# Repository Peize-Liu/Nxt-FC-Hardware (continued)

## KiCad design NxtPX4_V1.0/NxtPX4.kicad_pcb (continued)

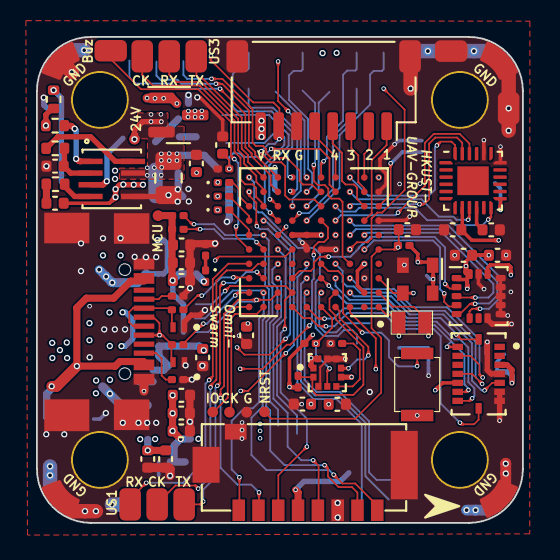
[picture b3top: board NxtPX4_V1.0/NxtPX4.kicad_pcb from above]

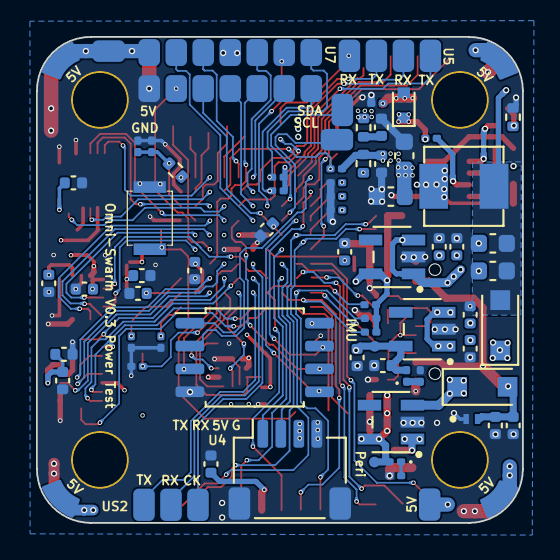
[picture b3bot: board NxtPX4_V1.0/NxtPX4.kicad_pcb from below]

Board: 4 copper layers, 27.0 x 27.0 mm, 150 parts (73 on the bottom side), 115 nets.

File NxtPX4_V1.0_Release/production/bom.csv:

Designator,Footprint,Quantity,Value,LCSC Part #
"BOOT1, RST1",3x2.5PushButton,2,TD-1183SN-1.5H(3x2.5),
C1,C_0805_2012Metric,1,22uF(0805 35V),
"C10, C16, C17, C19",C_0402_1005Metric,4,1uF(0402),
"C11, C12, C13, C14, C18, C20, C21, C22, C23, C24, C25, C28, C36, C39, C40, C42, C44, C46, C48, C49, C51, C6, C7, C8, C9",C_0402_1005Metric,25,100nF(0402),
"C15, C3, C41, C45",C_0402_1005Metric,4,10nF(0402),
"C2, C4",C_0603_1608Metric,2,10uF(0603 35V),
"C26, C27",C_0603_1608Metric,2,22uF(0603),
"C29, C30, C43",C_0402_1005Metric,3,2.2uF(0402),
C31,C_0402_1005Metric,1,4.7uF(0402),
C32,C_0402_1005Metric,1,15pF(0402),
C33,C_0402_1005Metric,1,1.0uF(0402),
C34,C_0201_0603Metric,1,100nF(0201),
C35,C_0201_0603Metric,1,1uF(0201),
"C37, C38",C_0201_0603Metric,2,12.0pF(0201),
"C47, C50",C_0402_1005Metric,2,100.0nF(0402),
C5,C_0402_1005Metric,1,1uF(0402 35V),
D1,PESD12VV1BL_315,1,PESD12VV1BL,
D10,LED_0201_0603Metric,1,LED_RED(0201),
D11,LED_0201_0603Metric,1,LED_BLUE(0201),
D12,LED_0201_0603Metric,1,LED_GREEN(0201),
"D2, D3",PESD5V0F1BL,2,PESD5V0F1BL,
D4,D_SOD-523,1,BZX584C9V1,
"D5, D6",D_SOD-123F,2,DSS34,
"D7, D8, D9",LED_0201_0603Metric,3,LED_G(0201),
J1,USB-C-16p,1,USB_C_Receptacle_USB2.0,
J10,JST_SH_SM08B-SRSS-TB_1x08-1MP_P1.00mm_Horizontal,1,ESC sh1.0 8pin,
J11,TF-SMD_TF-021B-H265,1,Micro_SD_Card,
J2,Conn_4Pin,1,Conn_01x04,
"J4, J5, J6",Conn_3pin,3,Conn_01x03,
J8,Conn_14pin,1,Conn_01x14,
J9,JST_SH_SM04B-SRSS-TB_1x04-1MP_P1.00mm_Horizontal,1,UART4(sh1.0 4pin),
L1,Inductor_0420,1,10uH(0420),
Q1,SOT-23,1,AP40P05,
"R1, R9",R_0402_1005Metric,2,33R(0402),
R10,R_0402_1005Metric,1,20R(0402),
R11,R_0402_1005Metric,1,51kR(0402),
R12,R_0402_1005Metric,1,7.68kR(0402),
R13,R_0402_1005Metric,1,41.2kR(0402),
R14,R_0201_0603Metric,1,200.0kR(0201),
R15,R_0201_0603Metric,1,22.0kR(0201),
"R16, R17, R18, R24, R26, R30, R31, R32, R33, R34",R_0201_0603Metric,10,10kR(0201),
"R19, R20, R27, R28",R_0201_0603Metric,4,4.7kR(0201),
"R2, R3",R_0201_0603Metric,2,5.1kR(0201),
"R21, R22, R23",R_0201_0603Metric,3,10.0kR(0201),
R25,R_0402_1005Metric,1,0.0R(0402),
"R29, R5, R6",R_0201_0603Metric,3,0R(0201),
R4,R_0201_0603Metric,1,100kR(0201),
R7,R_0201_0603Metric,1,1mR(0201),
R8,R_0402_1005Metric,1,100kR(0402),
"TP10, TP11, TP12, TP13, TP6, TP7, TP8, TP9",PWR_Circle,8,TestPoint,
"TP24, TP26, TP28",Conn_1pin,3,TestPoint,
TP25,Conn_1pin,1,5V_TP,
TP27,Conn_1pin,1,GND_TP,
"TP29, TP30, TP31, TP32",MiniTP,4,TestPoint,
TP5,MiniTP,1,24V_TP,
"U1, U2, U3",RT9013-33GB,3,RT9013-33GB,
U10,BMI088,1,BMI088,
U11,SOIC-8_5.23x5.23mm_P1.27mm,1,W25Q128JVS,
U4,MP9943GQ-Z,1,MP9943GQ-Z,
U6,STM32H743VIHBGA100C80P10X10_800X800X110N,1,STM32H743VIH6,
U7,QFN-24-1EP_3x3mm_P0.4mm_EP1.75x1.6mm,1,MPU6500,
U8,LGA-16_3x3mm_P0.5mm_LayoutBorder3x5y,1,ICM-20602,
U9,PQFN50P200X200X80-10N,1,BMP388,
Y1,Oscillator_SMD_Abracon_ASDMB-4Pin_2.5x2.0mm,1,SG-210STF,
Y2,LSE(2012),1,ABS07 (32.768kHZ),

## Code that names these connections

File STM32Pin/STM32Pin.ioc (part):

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Mcu.Name=STM32H743VITx
Mcu.Package=LQFP100
Mcu.UserName=STM32H743VITx
PA0.GPIOParameters=GPIO_Label,PinAttribute
PA0.GPIO_Label=PWM/DSHOT CH1
PA0.PinAttribute=Free
PA0.Signal=S_TIM5_CH1
PA1.GPIOParameters=GPIO_Label,PinAttribute
PA1.GPIO_Label=PWM/DSHOT CH2
PA1.PinAttribute=Free
PA1.Signal=S_TIM5_CH2
PA11.Mode=Device_Only
PA11.Signal=USB_OTG_FS_DM
PA12.Mode=Device_Only
PA12.Signal=USB_OTG_FS_DP
PA13\ (JTMS/SWDIO).Mode=Serial_Wire
PA13\ (JTMS/SWDIO).Signal=DEBUG_JTMS-SWDIO
PA14\ (JTCK/SWCLK).Mode=Serial_Wire
PA14\ (JTCK/SWCLK).Signal=DEBUG_JTCK-SWCLK
PA2.GPIOParameters=GPIO_Label,PinAttribute
PA2.GPIO_Label=PWM/DSHOT CH3
PA2.PinAttribute=Free
PA2.Signal=S_TIM5_CH3
PA3.GPIOParameters=GPIO_Label,PinAttribute
PA3.GPIO_Label=PWM/DSHOT CH4
PA3.PinAttribute=Free
PA3.Signal=S_TIM5_CH4
PA4.GPIOParameters=PinAttribute
PA4.Mode=Synchronous
PA4.PinAttribute=Free
PA4.Signal=USART2_CK
PA5.GPIOParameters=PinAttribute
PA5.Mode=Full_Duplex_Master
PA5.PinAttribute=Free
PA5.Signal=SPI1_SCK
PA6.GPIOParameters=PinAttribute
PA6.Mode=Full_Duplex_Master
PA6.PinAttribute=Free
PA6.Signal=SPI1_MISO
PA7.GPIOParameters=GPIO_Label,PinAttribute
PA7.GPIO_Label=MPU_Data_RDY
PA7.PinAttribute=Free
PA7.Signal=GPXTI7
PA8.Mode=Synchronous
PA8.Signal=USART1_CK
PA9.Mode=Full_Duplex_Master
PA9.Signal=SPI2_SCK
PB0.GPIOParameters=GPIO_Label,PinAttribute
PB0.GPIO_Label=BAT_V
PB0.PinAttribute=Free
PB0.Signal=ADCx_INP9
PB1.GPIOParameters=GPIO_Label,PinAttribute
PB1.GPIO_Label=BAT_I
PB1.PinAttribute=Free
PB1.Signal=ADCx_INP5
PB10.GPIOParameters=PinAttribute
PB10.Mode=I2C
PB10.PinAttribute=Free
PB10.Signal=I2C2_SCL
PB11.Mode=I2C
PB11.Signal=I2C2_SDA
PB12.GPIOParameters=PinAttribute
PB12.Mode=Asynchronous
PB12.PinAttribute=Free
PB12.Signal=UART5_RX
PB13.Mode=Asynchronous
PB13.Signal=UART5_TX
PB14.Mode=Synchronous
PB14.Signal=USART1_TX
PB15.Mode=Synchronous
PB15.Signal=USART1_RX
PB2.GPIOParameters=PinAttribute
PB2.Mode=Single Bank 1
PB2.PinAttribute=Free
PB2.Signal=QUADSPI_CLK
PB3\ (JTDO/TRACESWO).Mode=Full_Duplex_Master
PB3\ (JTDO/TRACESWO).Signal=SPI3_SCK
PB4\ (NJTRST).Mode=Full_Duplex_Master
PB4\ (NJTRST).Signal=SPI3_MISO
PB5.Mode=Full_Duplex_Master
PB5.Signal=SPI3_MOSI
PB6.Mode=Single Bank 1
PB6.Signal=QUADSPI_BK1_NCS
PB7.Mode=I2C
PB7.Signal=I2C1_SDA
PB8.Mode=I2C
PB8.Signal=I2C1_SCL
PB9.GPIOParameters=GPIO_Label
PB9.GPIO_Label=BMP_Data_RDY
PB9.Signal=GPXTI9
PC0.GPIOParameters=GPIO_Label
PC0.GPIO_Label=ICM_Data_RDY
PC0.Signal=GPXTI0
PC1.Mode=Full_Duplex_Master
PC1.Signal=SPI2_MOSI
PC10.Mode=SD_4_bits_Wide_bus
PC10.Signal=SDMMC1_D2
PC11.Mode=SD_4_bits_Wide_bus
PC11.Signal=SDMMC1_D3
PC12.Mode=SD_4_bits_Wide_bus
PC12.Signal=SDMMC1_CK
PC13.GPIOParameters=GPIO_Label
PC13.GPIO_Label=Extern_SPI_INT_2
PC13.Signal=GPIO_Input
PC14-OSC32_IN\ (OSC32_IN).Mode=LSE-External-Oscillator
PC14-OSC32_IN\ (OSC32_IN).Signal=RCC_OSC32_IN
PC15-OSC32_OUT\ (OSC32_OUT).Mode=LSE-External-Oscillator
PC15-OSC32_OUT\ (OSC32_OUT).Signal=RCC_OSC32_OUT
PC2_C.Mode=Full_Duplex_Master
PC2_C.Signal=SPI2_MISO
PC3_C.GPIOParameters=GPIO_Label,PinAttribute
PC3_C.GPIO_Label=ICM_NCS
PC3_C.PinAttribute=Free
PC3_C.Signal=GPIO_Output
PC4.GPIOParameters=GPIO_Label,PinAttribute
PC4.GPIO_Label=MPU_NCS
PC4.PinAttribute=Free
PC4.Signal=GPIO_Output
PC7.GPIOParameters=GPIO_Label
PC7.GPIO_Label=Buzzer
PC7.Signal=S_TIM3_CH2
PC8.Mode=SD_4_bits_Wide_bus
PC8.Signal=SDMMC1_D0
PC9.Mode=SD_4_bits_Wide_bus
PC9.Signal=SDMMC1_D1
PD0.Mode=Asynchronous
PD0.Signal=UART4_RX
PD1.Mode=Asynchronous
PD1.Signal=UART4_TX
PD10.Mode=Synchronous
PD10.Signal=USART3_CK
PD11.Mode=Single Bank 1
PD11.Signal=QUADSPI_BK1_IO0
PD12.Mode=Single Bank 1
PD12.Signal=QUADSPI_BK1_IO1
PD13.Mode=Single Bank 1
PD13.Signal=QUADSPI_BK1_IO3
PD14.GPIOParameters=GPIO_Label
PD14.GPIO_Label=PWM/DSHOT CH5
PD14.Signal=S_TIM4_CH3
PD15.GPIOParameters=GPIO_Label
PD15.GPIO_Label=PWM/DSHOT CH6 
PD15.Signal=S_TIM4_CH4
PD2.Mode=SD_4_bits_Wide_bus
PD2.Signal=SDMMC1_CMD
PD3.GPIOParameters=GPIO_Label
PD3.GPIO_Label=BMI_Accel_CS
PD3.Signal=GPIO_Output
PD4.GPIOParameters=GPIO_Label
PD4.GPIO_Label=BMI_Gyro_CS
PD4.Signal=GPIO_Output
PD5.Mode=Synchronous
PD5.Signal=USART2_TX
PD6.Mode=Synchronous
PD6.Signal=USART2_RX
PD7.Mode=Full_Duplex_Master
PD7.Signal=SPI1_MOSI
PD8.Mode=Synchronous
PD8.Signal=USART3_TX
PD9.Mode=Synchronous
PD9.Signal=USART3_RX
PE0.GPIOParameters=GPIO_Label
PE0.GPIO_Label=BMI_Accel_Data_RDY
PE0.Signal=GPIO_Output
PE1.GPIOParameters=GPIO_Label
PE1.GPIO_Label=BMI_Gyro_Data_RDY
PE1.Signal=GPIO_Output
PE11.GPIOParameters=GPIO_Label,PinAttribute
PE11.GPIO_Label=Extern_I2C_INT
PE11.PinAttribute=Free
PE11.Signal=GPXTI11
PE12.GPIOParameters=PinAttribute
PE12.Mode=Full_Duplex_Master
PE12.PinAttribute=Free
PE12.Signal=SPI4_SCK
PE13.GPIOParameters=GPIO_Label,PinAttribute
PE13.GPIO_Label=Status_LED_RED
PE13.PinAttribute=Free
PE13.Signal=GPIO_Output
PE14.GPIOParameters=GPIO_Label,PinAttribute
PE14.GPIO_Label=Status_LED_BLUE
PE14.PinAttribute=Free
PE14.Signal=GPIO_Analog
PE15.GPIOParameters=GPIO_Label,PinAttribute
PE15.GPIO_Label=Status_LED_GREEN
PE15.PinAttribute=Free
PE15.Signal=GPIO_Output
PE2.Mode=Single Bank 1
PE2.Signal=QUADSPI_BK1_IO2
PE3.GPIOParameters=GPIO_Label
PE3.GPIO_Label=Extern_SPI_INT_1
PE3.Signal=GPXTI3
PE4.GPIOParameters=GPIO_Label
PE4.GPIO_Label=Extern_SPI_CS_2
PE4.Signal=GPIO_Output
PE5.Mode=Full_Duplex_Master
PE5.Signal=SPI4_MISO
PE6.Mode=Full_Duplex_Master
PE6.Signal=SPI4_MOSI
PE7.GPIOParameters=PinAttribute
PE7.Mode=Asynchronous
PE7.PinAttribute=Free
PE7.Signal=UART7_RX
PE8.GPIOParameters=PinAttribute
PE8.Mode=Asynchronous
PE8.PinAttribute=Free
PE8.Signal=UART7_TX
PE9.GPIOParameters=GPIO_Label,PinAttribute
PE9.GPIO_Label=Extern_IMU_Heater
PE9.PinAttribute=Free
PE9.Signal=S_TIM1_CH1
PH0-OSC_IN\ (PH0).Mode=HSE-External-Clock-Source
PH0-OSC_IN\ (PH0).Signal=RCC_OSC_IN
PH1-OSC_OUT\ (PH1).GPIOParameters=GPIO_Label
PH1-OSC_OUT\ (PH1).GPIO_Label=Extern_SPI_CS_1
PH1-OSC_OUT\ (PH1).Signal=GPIO_Output
RCC.HSE_VALUE=16000000
RCC.SYSCLKFreq_VALUE=480000000
RCC.SYSCLKSource=RCC_SYSCLKSOURCE_PLLCLK
board=custom

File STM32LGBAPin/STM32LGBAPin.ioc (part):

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Mcu.Name=STM32H743V(G-I)Hx
Mcu.Package=TFBGA100
Mcu.UserName=STM32H743VIHx
PA0.Signal=S_TIM5_CH1
PA1.Signal=S_TIM5_CH2
PA10.Mode=Synchronous
PA10.Signal=USART1_RX
PA11.Mode=Device_Only
PA11.Signal=USB_OTG_FS_DM
PA12.Mode=Device_Only
PA12.Signal=USB_OTG_FS_DP
PA13\ (JTMS/SWDIO).Mode=Serial_Wire
PA13\ (JTMS/SWDIO).Signal=DEBUG_JTMS-SWDIO
PA14\ (JTCK/SWCLK).Mode=Serial_Wire
PA14\ (JTCK/SWCLK).Signal=DEBUG_JTCK-SWCLK
PA2.Signal=S_TIM5_CH3
PA3.Signal=S_TIM5_CH4
PA4.GPIOParameters=GPIO_Label
PA4.GPIO_Label=SPI2_Data_RDY
PA4.Signal=GPXTI4
PA5.Mode=Full_Duplex_Master
PA5.Signal=SPI1_SCK
PA6.Mode=Full_Duplex_Master
PA6.Signal=SPI1_MISO
PA7.Mode=Full_Duplex_Master
PA7.Signal=SPI1_MOSI
PA8.Mode=Synchronous
PA8.Signal=USART1_CK
PA9.Mode=Synchronous
PA9.Signal=USART1_TX
PB0.GPIOParameters=GPIO_Label
PB0.GPIO_Label=BAT_V
PB0.Signal=ADCx_INP9
PB1.GPIOParameters=GPIO_Label
PB1.GPIO_Label=BAT_I
PB1.Signal=ADCx_INP5
PB10.Mode=I2C
PB10.Signal=I2C2_SCL
PB11.Mode=I2C
PB11.Signal=I2C2_SDA
PB12.Mode=Asynchronous
PB12.Signal=UART5_RX
PB13.Mode=Asynchronous
PB13.Signal=UART5_TX
PB14.GPIOParameters=GPIO_Label
PB14.GPIO_Label=LED_Green
PB14.Signal=GPIO_Output
PB15.GPIOParameters=GPIO_Label
PB15.GPIO_Label=LED_BLUE
PB15.Signal=GPIO_Output
PB2.Mode=Single Bank 1
PB2.Signal=QUADSPI_CLK
PB3\ (JTDO/TRACESWO).Mode=Full_Duplex_Master
PB3\ (JTDO/TRACESWO).Signal=SPI3_SCK
PB4\ (NJTRST).Mode=Full_Duplex_Master
PB4\ (NJTRST).Signal=SPI3_MISO
PB5.Mode=Full_Duplex_Master
PB5.Signal=SPI3_MOSI
PB6.Mode=Single Bank 1
PB6.Signal=QUADSPI_BK1_NCS
PB7.Mode=I2C
PB7.Signal=I2C1_SDA
PB8.Mode=I2C
PB8.Signal=I2C1_SCL
PB9.GPIOParameters=GPIO_Label
PB9.GPIO_Label=I2C1_Data_RDY
PB9.Signal=GPXTI9
PC1.Mode=Full_Duplex_Master
PC1.Signal=SPI2_MOSI
PC10.Mode=SD_4_bits_Wide_bus
PC10.Signal=SDMMC1_D2
PC11.Mode=SD_4_bits_Wide_bus
PC11.Signal=SDMMC1_D3
PC12.Mode=SD_4_bits_Wide_bus
PC12.Signal=SDMMC1_CK
PC14-OSC32_IN\ (OSC32_IN).Mode=LSE-External-Oscillator
PC14-OSC32_IN\ (OSC32_IN).Signal=RCC_OSC32_IN
PC15-OSC32_OUT\ (OSC32_OUT).Mode=LSE-External-Oscillator
PC15-OSC32_OUT\ (OSC32_OUT).Signal=RCC_OSC32_OUT
PC2_C.Mode=Full_Duplex_Master
PC2_C.Signal=SPI2_MISO
PC3_C.GPIOParameters=GPIO_Label
PC3_C.GPIO_Label=SPI2_NCS
PC3_C.Signal=GPIO_Output
PC4.GPIOParameters=GPIO_Label
PC4.GPIO_Label=SPI1_NCS
PC4.Signal=GPIO_Output
PC5.GPIOParameters=GPIO_Label
PC5.GPIO_Label=SPI1_Data_RDY
PC5.Signal=GPXTI5
PC6.GPIOParameters=GPIO_Label
PC6.GPIO_Label=LED_RED
PC6.Signal=GPIO_Output
PC7.GPIOParameters=GPIO_Label
PC7.GPIO_Label=Buzzer
PC7.Signal=S_TIM3_CH2
PC8.Mode=SD_4_bits_Wide_bus
PC8.Signal=SDMMC1_D0
PC9.Mode=SD_4_bits_Wide_bus
PC9.Signal=SDMMC1_D1
PD0.Mode=Asynchronous
PD0.Signal=UART4_RX
PD1.Mode=Asynchronous
PD1.Signal=UART4_TX
PD10.Mode=Synchronous
PD10.Signal=USART3_CK
PD11.Mode=Single Bank 1
PD11.Signal=QUADSPI_BK1_IO0
PD12.Mode=Single Bank 1
PD12.Signal=QUADSPI_BK1_IO1
PD13.Mode=Single Bank 1
PD13.Signal=QUADSPI_BK1_IO3
PD14.Signal=S_TIM4_CH3
PD15.Signal=S_TIM4_CH4
PD2.Mode=SD_4_bits_Wide_bus
PD2.Signal=SDMMC1_CMD
PD3.Mode=Full_Duplex_Master
PD3.Signal=SPI2_SCK
PD5.Mode=Synchronous
PD5.Signal=USART2_TX
PD6.Mode=Synchronous
PD6.Signal=USART2_RX
PD7.Mode=Synchronous
PD7.Signal=USART2_CK
PD8.Mode=Synchronous
PD8.Signal=USART3_TX
PD9.Mode=Synchronous
PD9.Signal=USART3_RX
PE0.GPIOParameters=GPIO_Label
PE0.GPIO_Label=SPI3_Gyro_Data_RDY
PE0.Signal=GPXTI0
PE1.GPIOParameters=GPIO_Label
PE1.GPIO_Label=SPI3_Accel_Data_RDY
PE1.Signal=GPXTI1
PE10.GPIOParameters=GPIO_Label
PE10.GPIO_Label=SPI4_INT_1
PE10.Signal=GPXTI10
PE11.GPIOParameters=GPIO_Label
PE11.GPIO_Label=SPI4_INT_2
PE11.Signal=GPXTI11
PE12.Mode=Full_Duplex_Master
PE12.Signal=SPI4_SCK
PE13.GPIOParameters=GPIO_Label
PE13.GPIO_Label=SPI4_CS_1
PE13.Signal=GPXTI13
PE14.GPIOParameters=GPIO_Label
PE14.GPIO_Label=SPI4_CS_2
PE14.Signal=GPIO_Output
PE15.GPIOParameters=GPIO_Label
PE15.GPIO_Label=I2C2_INT
PE15.Signal=GPXTI15
PE2.Mode=Single Bank 1
PE2.Signal=QUADSPI_BK1_IO2
PE3.GPIOParameters=GPIO_Label
PE3.GPIO_Label=SPI3_Accel_CS
PE3.Signal=GPIO_Output
PE4.GPIOParameters=GPIO_Label
PE4.GPIO_Label=SPI3_Gyro_CS
PE4.Signal=GPIO_Output
PE5.Mode=Full_Duplex_Master
PE5.Signal=SPI4_MISO
PE6.Mode=Full_Duplex_Master
PE6.Signal=SPI4_MOSI
PE7.Mode=Asynchronous
PE7.Signal=UART7_RX
PE8.Mode=Asynchronous
PE8.Signal=UART7_TX
PE9.GPIOParameters=GPIO_Label
PE9.GPIO_Label=PWM_Heat
PE9.Signal=S_TIM1_CH1
PH0-OSC_IN\ (PH0).Mode=HSE-External-Clock-Source
PH0-OSC_IN\ (PH0).Signal=RCC_OSC_IN
RCC.HSE_VALUE=16000000
RCC.SYSCLKFreq_VALUE=48000000
RCC.SYSCLKSource=RCC_SYSCLKSOURCE_PLLCLK
board=custom

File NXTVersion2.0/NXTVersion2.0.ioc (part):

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Mcu.Name=STM32H743V(G-I)Hx
Mcu.Package=TFBGA100
Mcu.UserName=STM32H743VIHx
PA0.GPIOParameters=GPIO_Label
PA0.GPIO_Label=SPI1_ADR
PA0.Signal=GPXTI0
PA1.GPIOParameters=GPIO_Label
PA1.GPIO_Label=SPI1_GDR
PA1.Signal=GPXTI1
PA10.Mode=Asynchronous
PA10.Signal=USART1_RX
PA11.Mode=Device_Only
PA11.Signal=USB_OTG_FS_DM
PA12.Mode=Device_Only
PA12.Signal=USB_OTG_FS_DP
PA13\ (JTMS/SWDIO).Mode=Serial_Wire
PA13\ (JTMS/SWDIO).Signal=DEBUG_JTMS-SWDIO
PA14\ (JTCK/SWCLK).Mode=Serial_Wire
PA14\ (JTCK/SWCLK).Signal=DEBUG_JTCK-SWCLK
PA2.GPIOParameters=GPIO_Label
PA2.GPIO_Label=SPI1_ACS
PA2.Signal=GPIO_Output
PA3.GPIOParameters=GPIO_Label
PA3.GPIO_Label=SPI1_GCS
PA3.Signal=GPIO_Output
PA4.GPIOParameters=GPIO_Label
PA4.GPIO_Label=AUX3
PA4.Signal=GPIO_Output
PA5.Mode=Full_Duplex_Master
PA5.Signal=SPI1_SCK
PA6.Mode=Full_Duplex_Master
PA6.Signal=SPI1_MISO
PA7.Mode=Full_Duplex_Master
PA7.Signal=SPI1_MOSI
PA9.Mode=Asynchronous
PA9.Signal=USART1_TX
PB0.Signal=S_TIM3_CH3
PB1.Signal=S_TIM3_CH4
PB10.Signal=S_TIM2_CH3
PB11.Signal=S_TIM2_CH4
PB12.Mode=Asynchronous
PB12.Signal=UART5_RX
PB13.Mode=Asynchronous
PB13.Signal=UART5_TX
PB14.Mode=Full_Duplex_Master
PB14.Signal=SPI2_MISO
PB15.GPIOParameters=GPIO_Label
PB15.GPIO_Label=LED_R
PB15.Signal=GPIO_Output
PB2.Mode=Full_Duplex_Master
PB2.Signal=SPI3_MOSI
PB3\ (JTDO/TRACESWO).Mode=Full_Duplex_Master
PB3\ (JTDO/TRACESWO).Signal=SPI3_SCK
PB4\ (NJTRST).Mode=Full_Duplex_Master
PB4\ (NJTRST).Signal=SPI3_MISO
PB5.GPIOParameters=GPIO_Label
PB5.GPIO_Label=BARO_DR
PB5.Signal=GPXTI5
PB6.Mode=I2C
PB6.Signal=I2C1_SCL
PB7.Mode=I2C
PB7.Signal=I2C1_SDA
PB8.Mode=Asynchronous
PB8.Signal=UART4_RX
PB9.Mode=Asynchronous
PB9.Signal=UART4_TX
PC0.GPIOParameters=GPIO_Label
PC0.GPIO_Label=AUX2
PC0.Signal=GPIO_Output
PC1.GPIOParameters=GPIO_Label
PC1.GPIO_Label=AUX1
PC1.Signal=GPIO_Output
PC10.Mode=SD_4_bits_Wide_bus
PC10.Signal=SDMMC1_D2
PC11.Mode=SD_4_bits_Wide_bus
PC11.Signal=SDMMC1_D3
PC12.Mode=SD_4_bits_Wide_bus
PC12.Signal=SDMMC1_CK
PC13.GPIOParameters=GPIO_Label
PC13.GPIO_Label=SPI4_ACS
PC13.Signal=GPIO_Output
PC14-OSC32_IN\ (OSC32_IN).Mode=LSE-External-Oscillator
PC14-OSC32_IN\ (OSC32_IN).Signal=RCC_OSC32_IN
PC15-OSC32_OUT\ (OSC32_OUT).Mode=LSE-External-Oscillator
PC15-OSC32_OUT\ (OSC32_OUT).Signal=RCC_OSC32_OUT
PC2_C.GPIOParameters=GPIO_Label
PC2_C.GPIO_Label=SPI4_GCS
PC2_C.Signal=GPIO_Output
PC3_C.Mode=Full_Duplex_Master
PC3_C.Signal=SPI2_MOSI
PC4.Signal=ADCx_INP4
PC5.GPIOParameters=GPIO_Label
PC5.GPIO_Label=ADC_I
PC5.Signal=ADCx_INP8
PC6.Mode=Asynchronous
PC6.Signal=USART6_TX
PC7.Mode=Asynchronous
PC7.Signal=USART6_RX
PC8.Mode=SD_4_bits_Wide_bus
PC8.Signal=SDMMC1_D0
PC9.Mode=SD_4_bits_Wide_bus
PC9.Signal=SDMMC1_D1
PD0.Signal=GPIO_Input
PD11.GPIOParameters=GPIO_Label
PD11.GPIO_Label=LED_G
PD11.Signal=GPIO_Output
PD12.Mode=I2C
PD12.Signal=I2C4_SCL
PD13.Mode=I2C
PD13.Signal=I2C4_SDA
PD15.GPIOParameters=GPIO_Label
PD15.GPIO_Label=LED_B
PD15.Signal=GPIO_Output
PD2.Mode=SD_4_bits_Wide_bus
PD2.Signal=SDMMC1_CMD
PD3.Mode=Full_Duplex_Master
PD3.Signal=SPI2_SCK
PD4.GPIOParameters=GPIO_Label
PD4.GPIO_Label=FRAM_CS
PD4.Signal=GPIO_Output
PD5.Mode=Asynchronous
PD5.Signal=USART2_TX
PD6.Mode=Asynchronous
PD6.Signal=USART2_RX
PD8.Mode=Asynchronous
PD8.Signal=USART3_TX
PD9.Mode=Asynchronous
PD9.Signal=USART3_RX
PE0.Mode=Asynchronous
PE0.Signal=UART8_RX
PE1.Mode=Asynchronous
PE1.Signal=UART8_TX
PE11.Signal=S_TIM1_CH2
PE13.Signal=S_TIM1_CH3
PE14.Signal=S_TIM1_CH4
PE2.Mode=Full_Duplex_Master
PE2.Signal=SPI4_SCK
PE3.Signal=GPXTI3
PE4.GPIOParameters=GPIO_Label
PE4.GPIO_Label=SPI4_GDR
PE4.Signal=GPXTI4
PE5.Mode=Full_Duplex_Master
PE5.Signal=SPI4_MISO
PE6.Mode=Full_Duplex_Master
PE6.Signal=SPI4_MOSI
PE7.Mode=Asynchronous
PE7.Signal=UART7_RX
PE8.Mode=Asynchronous
PE8.Signal=UART7_TX
PE9.Signal=S_TIM1_CH1
PH0-OSC_IN\ (PH0).Mode=HSE-External-Clock-Source
PH0-OSC_IN\ (PH0).Signal=RCC_OSC_IN
RCC.SYSCLKFreq_VALUE=10000000
RCC.SYSCLKSource=RCC_SYSCLKSOURCE_PLLCLK
board=custom

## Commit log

2023-01-08 Init:Init NxtPX4 hardware repo
2023-01-08 doc:add readme
2023-02-06 [Feat][other]:Release first version of hardware design
2023-03-03 [Feat][other]:Release V1.0 hardware design all need fucntion test pass
2023-03-03 [Fix][other]:ignore fp-lib-table and sym-lib-tatle
2023-03-03 [Fix][other]:Upgrade for JLC manufacturer
2023-03-03 [Doc][other]:Readme information add
2023-03-22 [Doc][other]: add caution info
2023-03-23 [Fix][hardware]:v1.1.0 change esc pinout order
2023-03-23 [Doc][hardware_design]:readme notice for v1.1.0 design
2023-03-26 [Doc][other]:readme add uart define
2023-03-26 [Doc][readme]: add v1.1.0 board img
2023-05-04 [Feat][Release]:Release v1.2.0 hardware
2023-05-04 [Doc][readme]:add v1.2.0 info
2023-05-21 [Doc][image]:add image
2023-12-12 [Feat][new version]: update hardware v2.0 Dual
2024-07-04 [Rlease][Dual]: Update logo for Dual version
